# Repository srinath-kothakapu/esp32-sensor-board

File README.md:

# ESP32 Sensor Board (BME280)

A compact 40 × 60 mm, 2-layer board with an ESP32-WROOM-32 and a Bosch BME280 for temperature, humidity and pressure. It runs from a 5 V input. Designed in KiCad 7.

## Schematic

## Overview

| Block | Parts | Notes |
|---|---|---|
| Power | J1, C1, U2 (AMS1117-3.3), C2, C3 | 5 V in, 3.3 V rail for MCU and sensor |
| MCU | U1 (ESP32-WROOM-32), R1, C4, SW1, SW2 | Reset (EN) and boot (GPIO0) buttons |
| Sensor | U3 (BME280), C5, R2, R3 | I2C, address 0x76 |
| Status LED | R4, D1 | Green LED on GPIO2 |
| Programming | J2 (GND / TX / RX) | 3.3 V USB-UART adapter |

### Pin map

| Signal | ESP32 | Connected to |
|---|---|---|
| SDA | GPIO21 | BME280 SDI, 4.7 k pull-up |
| SCL | GPIO22 | BME280 SCK, 4.7 k pull-up |
| LED | GPIO2 | 1 k → D1 → GND |
| BOOT | GPIO0 | SW2 to GND |
| EN | EN | 10 k pull-up, 1 µF to GND, SW1 to GND |
| UART | GPIO1 / GPIO3 | J2 |

The BME280 has CSB tied to 3.3 V (I2C mode) and SDO to GND, which gives address **0x76**.

## Design notes

- **Regulator:** AMS1117-3.3, cheap and simple for 5 V input. Being linear, it isn't efficient, so a buck converter would be better for battery use.
- **Reset:** the 10 k + 1 µF RC on EN gives a clean power-on reset. The ESP32 needs EN to rise after the supply is stable.
- **Boot mode:** hold SW2 (GPIO0 low) during reset to enter the serial bootloader.
- **Antenna:** the module overhangs the top edge, with a copper keepout under the antenna area.
- **Ground:** pours on both layers, stitched with vias.

## Verification

- Schematic-to-PCB netlist matches: 52/52 connections.
- KiCad DRC at 0.2 mm clearance: 0 errors, 19 warnings ([report](docs/drc_report.txt)). The warnings are the intentional antenna overhang and footprint library paths.
- Still to do: ERC, manufacturer DFM check, and a hardware bring-up.

## Known issues

- C2 (22 µF on the AMS1117 output) should be tantalum or low-ESR. Some AMS1117 parts can oscillate with pure ceramic.
- The BME280 is a 2.5 × 2.5 mm LGA, which isn't hand-solderable. It needs hot air or a breakout module.
- No USB or auto-reset circuit, so flashing needs the BOOT button and an external adapter.
- No reverse-polarity or over-current protection on the 5 V input.
- The ground zones are saved unfilled. Press **B** in the PCB editor to refill them.

## Roadmap

- [ ] Re-route the board by hand in KiCad
- [ ] Fix C2 and run ERC + DFM
- [ ] Add USB-C with a CP2102/CH340 and auto-reset
- [ ] Replace the LDO with a buck converter
- [ ] Order prototypes and write a firmware test (read the BME280, blink the LED)

## Repository layout

```
hardware/   KiCad 7 project, schematic and PCB
docs/       BOM, DRC report, images
```

## Opening the project

Install KiCad 7 or newer and open `hardware/esp32-sensor-board.kicad_pro`.

## Author

Srinath Reddy Kothakapu, M.Sc. Sensor Systems Technology, Hochschule Karlsruhe

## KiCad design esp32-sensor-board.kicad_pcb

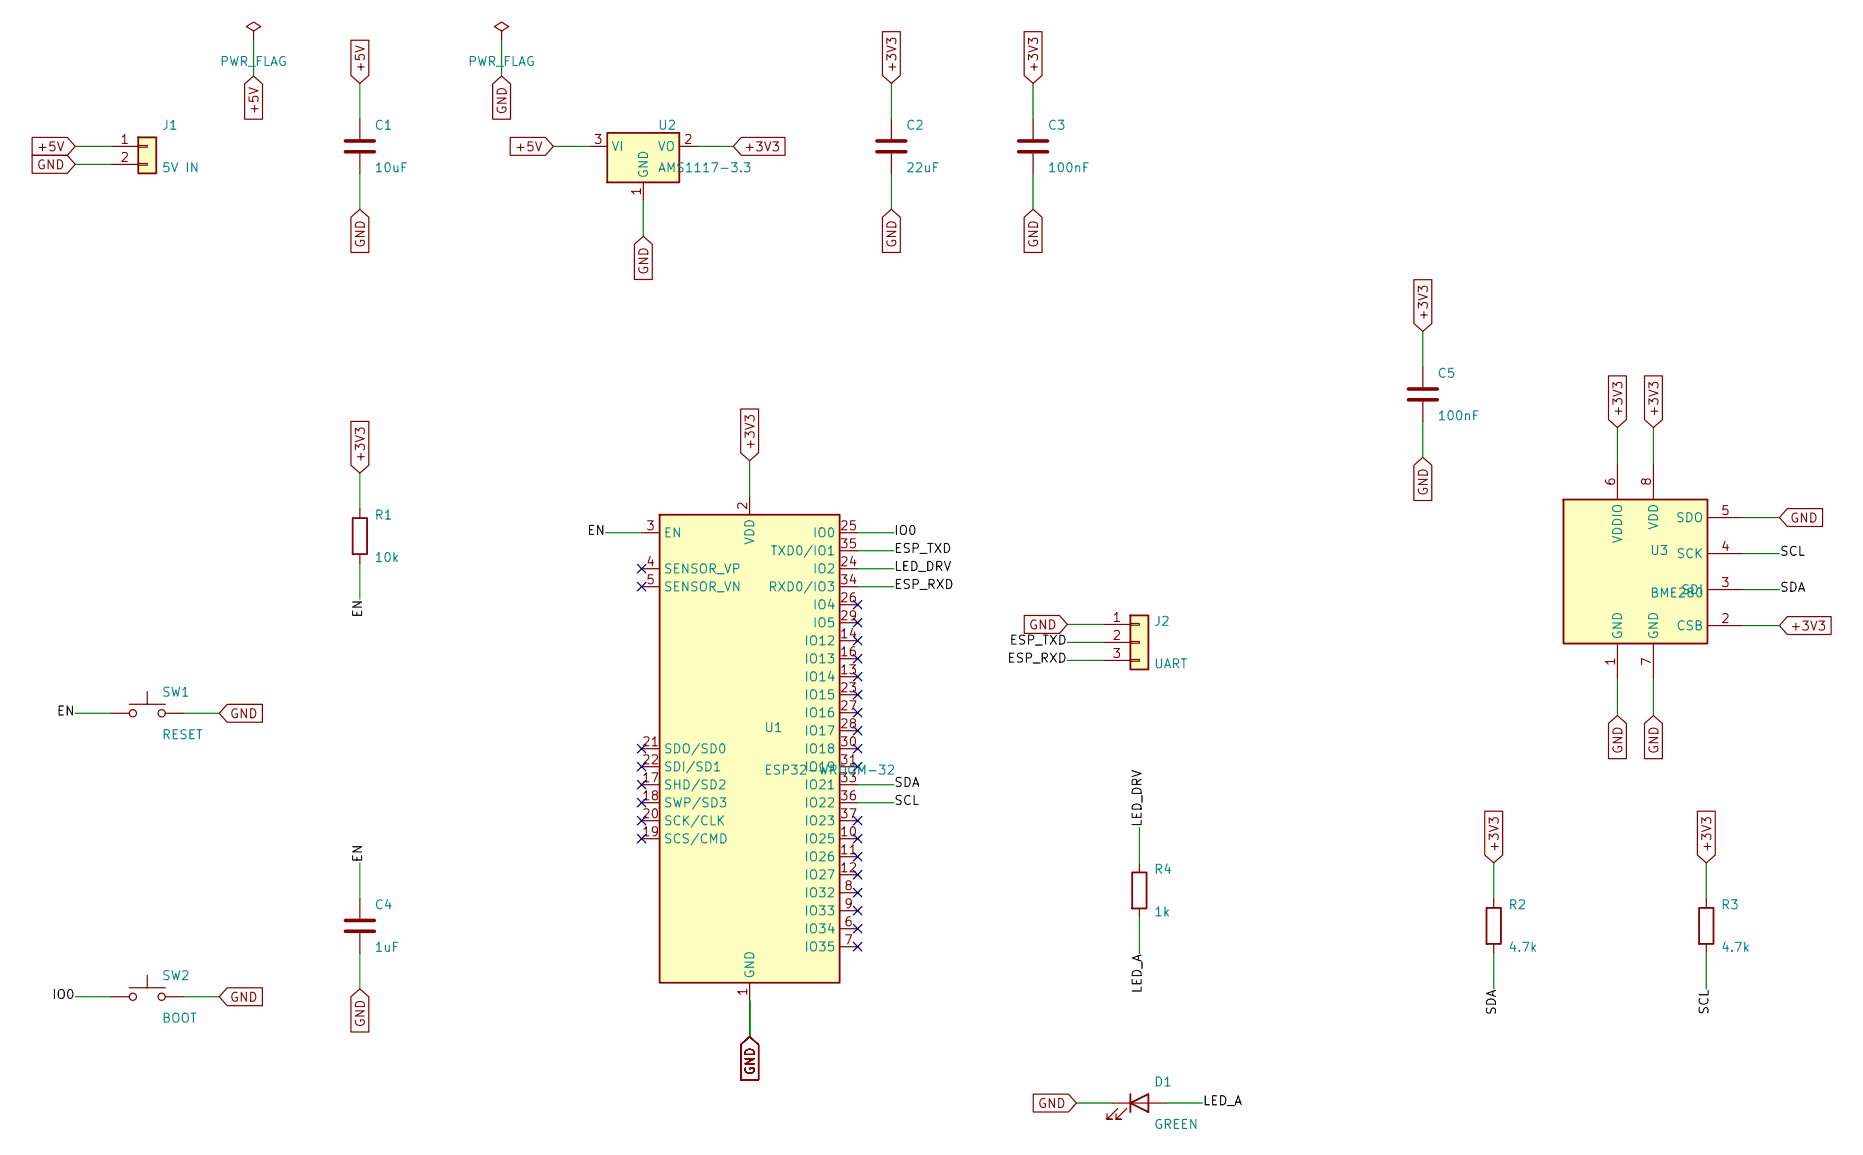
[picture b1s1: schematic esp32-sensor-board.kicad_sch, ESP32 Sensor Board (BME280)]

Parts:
C1: 10uF; C_0805_2012Metric
C2: 22uF; C_1206_3216Metric
C3, C5: 100nF; C_0603_1608Metric
C4: 1uF; C_0603_1608Metric
D1: GREEN; LED_0603_1608Metric
J1: 5V IN; PinHeader_1x02_P2.54mm_Vertical
J2: UART; PinHeader_1x03_P2.54mm_Vertical
R1: 10k; R_0603_1608Metric
R2, R3: 4.7k; R_0603_1608Metric
R4: 1k; R_0603_1608Metric
SW1: RESET; SW_SPST_B3U-1000P
SW2: BOOT; SW_SPST_B3U-1000P
U1: ESP32-WROOM-32
U2: AMS1117-3.3; SOT-223-3_TabPin2
U3: BME280; Bosch_LGA-8_2.5x2.5mm_P0.65mm_ClockwisePinNumbering

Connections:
+3V3: C2.1, C3.1, C5.1, R1.1, R2.1, R3.1, U1.2 (VDD), U2.2 (VO), U3.2 (CSB), U3.6 (VDDIO), U3.8 (VDD)
+5V: C1.1, J1.1, U2.3 (VI)
EN: C4.1, R1.2, SW1.1, U1.3 (EN)
ESP_RXD: J2.3, U1.34 (RXD0/IO3)
ESP_TXD: J2.2, U1.35 (TXD0/IO1)
GND: C1.2, C2.2, C3.2, C4.2, C5.2, D1.1 (K), J1.2, J2.1, SW1.2, SW2.2, U1.1 (GND), U1.15 (GND), U1.38 (GND), U1.39 (GND), U2.1 (GND), U3.1 (GND), U3.5 (SDO), U3.7 (GND)
IO0: SW2.1, U1.25 (IO0)
LED_A: D1.2 (A), R4.2
LED_DRV: R4.1, U1.24 (IO2)
SCL: R3.2, U1.36 (IO22), U3.4 (SCK)
SDA: R2.2, U1.33 (IO21), U3.3 (SDI)

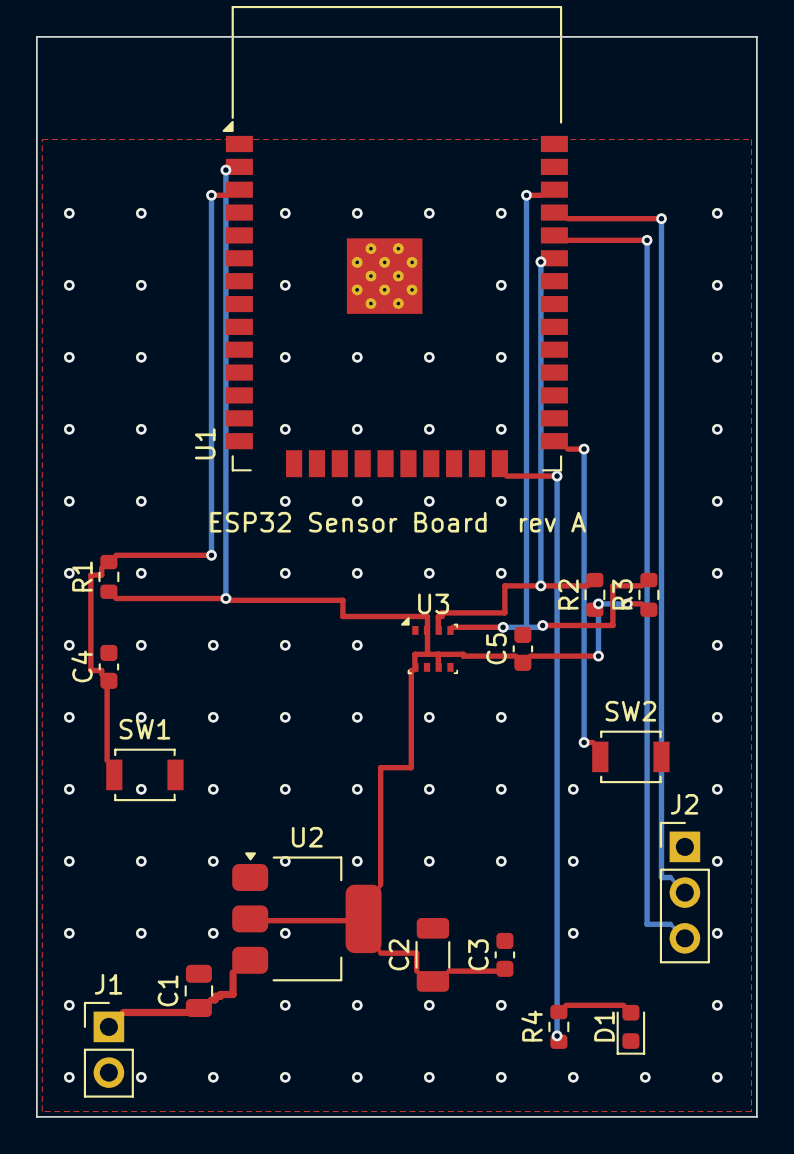
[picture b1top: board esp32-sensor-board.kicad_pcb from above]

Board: 2 copper layers, 40.0 x 60.0 mm, 17 parts (0 on the bottom side), 11 nets.

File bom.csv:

Ref,Value,Footprint,Qty,Note
U1,ESP32-WROOM-32,RF_Module:ESP32-WROOM-32,1,Wi-Fi/Bluetooth module (antenna overhangs board edge)
U2,AMS1117-3.3,Package_TO_SOT_SMD:SOT-223-3_TabPin2,1,3.3 V linear regulator
U3,BME280,Package_LGA:Bosch_LGA-8_2.5x2.5mm_P0.65mm_ClockwisePinNumbering,1,Temperature / humidity / pressure sensor (I2C 0x76)
C1,10uF,Capacitor_SMD:C_0805_2012Metric,1,5 V input capacitor
C2,22uF,Capacitor_SMD:C_1206_3216Metric,1,3.3 V output capacitor (use tantalum or low-ESR type with AMS1117)
"C3 C5",100nF,Capacitor_SMD:C_0603_1608Metric,2,Decoupling (ESP32 and BME280)
C4,1uF,Capacitor_SMD:C_0603_1608Metric,1,EN reset delay
R1,10k,Resistor_SMD:R_0603_1608Metric,1,EN pull-up
"R2 R3",4.7k,Resistor_SMD:R_0603_1608Metric,2,I2C pull-ups (SDA / SCL)
R4,1k,Resistor_SMD:R_0603_1608Metric,1,LED current limit
D1,GREEN,LED_SMD:LED_0603_1608Metric,1,Status LED on GPIO2
"SW1 SW2",SPST push,Button_Switch_SMD:SW_SPST_B3U-1000P,2,RESET (EN) and BOOT (GPIO0)
J1,5V IN,Connector_PinHeader_2.54mm:PinHeader_1x02_P2.54mm_Vertical,1,Power input (5 V / GND)
J2,UART,Connector_PinHeader_2.54mm:PinHeader_1x03_P2.54mm_Vertical,1,GND / TXD / RXD for flashing
